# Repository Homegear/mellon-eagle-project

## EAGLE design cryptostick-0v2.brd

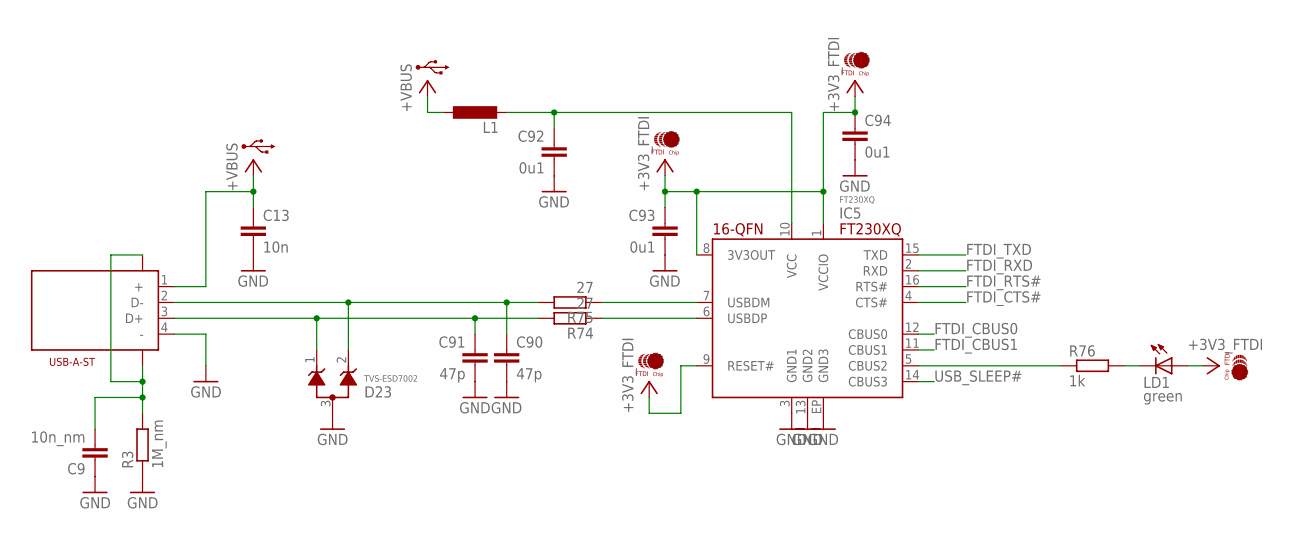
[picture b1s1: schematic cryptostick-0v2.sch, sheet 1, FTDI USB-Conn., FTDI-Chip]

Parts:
C9: 10n_nm; C0603
C13: 10n; R0402-MCU
C90, C91: 47p; R0402-MCU
C92, C93, C94: 0u1; R0402-MCU
D23: TVS-ESD7002; SC70-3
IC5: FT230XQ; 16QFN-FT230X
J1: USB-A-ST
L1: L-EUR0402-MCU; R0402-MCU
LD1: green; 0603-SIDELED-RPI
R3: 1M_nm; R0603
R74, R75: 27; R0402-MCU
R76: 1k; R0402-MCU

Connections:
+3V3_FTDI: C93.1, C94.1, IC5.1 (VCCIO), IC5.8 (3V3OUT), IC5.9 (RESET#), LD1.A; also elsewhere on the board
+5V_FTDI: C92.1, IC5.10 (VCC), L1.2
+VBUS: C13.1, J1.1 (+), L1.1; also elsewhere on the board
FTDI_CBUS0: IC5.12 (CBUS0); also elsewhere on the board
FTDI_CBUS1: IC5.11 (CBUS1); also elsewhere on the board
FTDI_CTS#: IC5.4 (CTS#); also elsewhere on the board
FTDI_RTS#: IC5.16 (RTS#); also elsewhere on the board
FTDI_RXD: IC5.2 (RXD); also elsewhere on the board
FTDI_TXD: IC5.15 (TXD); also elsewhere on the board
FTDI_TXLED#: IC5.5 (CBUS2), R76.1
GND: C9.1, C13.2, C90.2, C91.2, C92.2, C93.2, C94.2, D23.3, IC5.3 (GND1), IC5.13 (GND2), IC5.EP (GND3), J1.4 (-), R3.1; also elsewhere on the board
unnamed: LD1.C, R76.2
unnamed: IC5.7 (USBDM), R75.1
unnamed: IC5.6 (USBDP), R74.1
unnamed: C91.1, D23.1, J1.3 (D+), R74.2
unnamed: C90.1, D23.2, J1.2 (D-), R75.2
USB_SHLD: C9.2, J1.SH1, J1.SH2, R3.2
USB_SLEEP#: IC5.14 (CBUS3); also elsewhere on the board

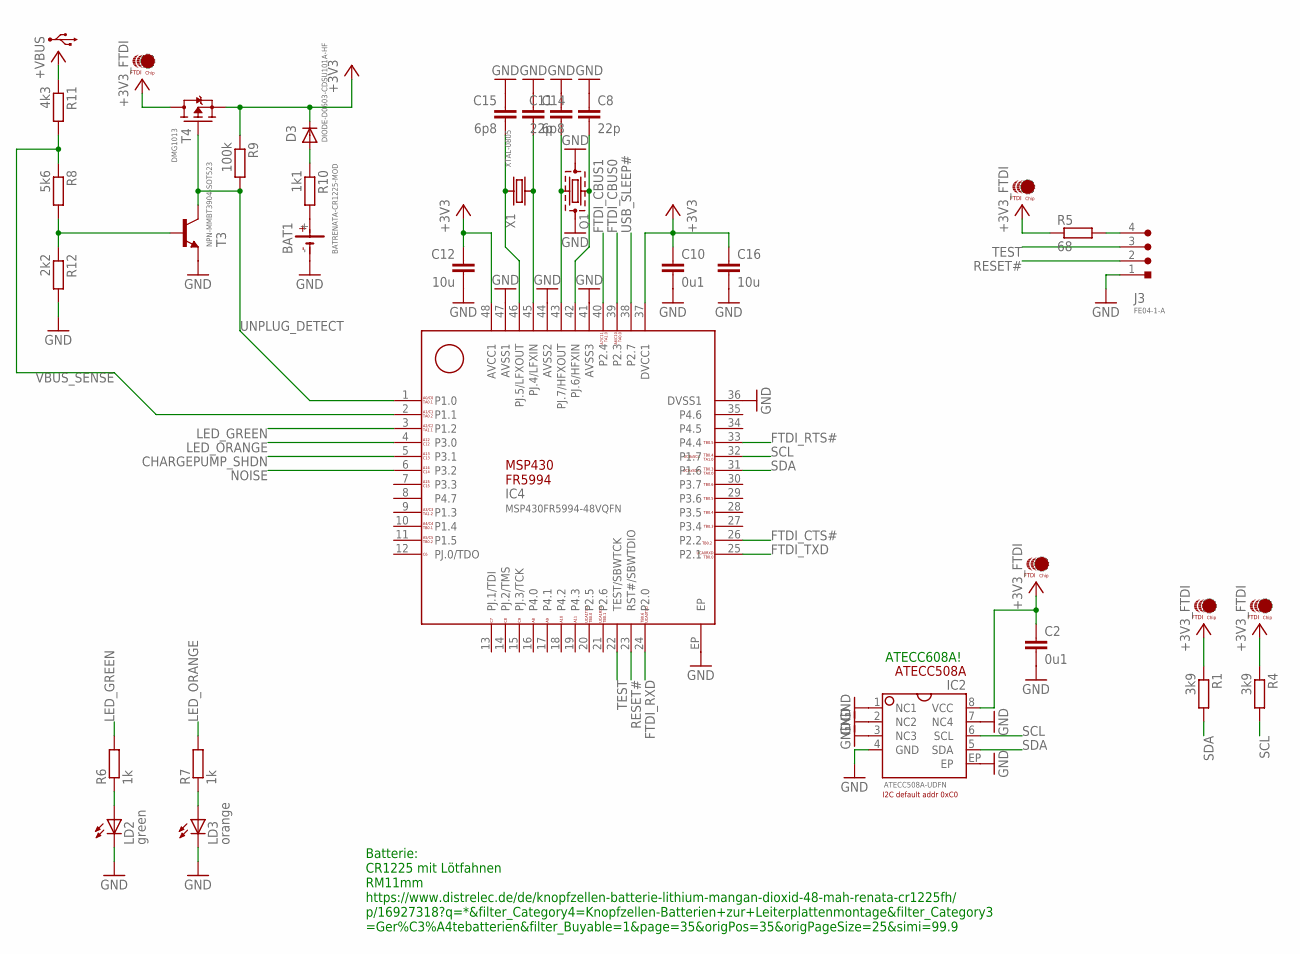
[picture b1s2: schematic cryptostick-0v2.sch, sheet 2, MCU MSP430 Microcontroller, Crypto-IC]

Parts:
BAT1: BATRENATA-CR1225-MOD; BAT-RENATA-CR1225-MOD
C2, C10: 0u1; R0402-MCU
C8, C11: 22p; R0402-MCU
C12, C16: 10u; R0603-MCU
C14, C15: 6p8; R0402-MCU
D3: DIODE-D0603-CDSU101A-HF; D-D0603
IC2: ATECC508A-UDFN; 8UDFN
IC4: MSP430FR5994-48VQFN; 48VQFN-MSP430FR5994
J3: FE04-1-A; FE04-1A
LD2: green; 0603-SIDELED-RPI
LD3: orange; 0603-SIDELED-RPI
Q1: XTAL-2.0X1.6-MOD
R1, R4: 3k9; R0402-MCU
R5: 68; R0402-MCU
R6, R7: 1k; R0402-MCU
R8: 5k6; R0402-MCU
R9: 100k; R0402-MCU
R10: 1k1; R0402-MCU
R11: 4k3; R0402-MCU
R12: 2k2; R0402-MCU
T3: NPN-MMBT3904-SOT523; SOT523
T4: DMG1013; SC70-3
X1: XTAL-0805; XTAL-32KHZ-0805

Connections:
+3V3: C10.1, C12.1, C16.1, D3.C, IC4.37 (DVCC1), IC4.48 (AVCC1), R9.1, T4.2 (S)
+3V3_FTDI: C2.1, IC2.8 (VCC), R1.1, R4.1, R5.1, T4.3 (D); also elsewhere on the board
+VBUS: R11.1; also elsewhere on the board
CHARGEPUMP_SHDN: IC4.5 (P3.1); also elsewhere on the board
FTDI_CBUS0: IC4.39 (P2.3); also elsewhere on the board
FTDI_CBUS1: IC4.40 (P2.4); also elsewhere on the board
FTDI_CTS#: IC4.26 (P2.2); also elsewhere on the board
FTDI_RTS#: IC4.33 (P4.4); also elsewhere on the board
FTDI_RXD: IC4.24 (P2.0); also elsewhere on the board
FTDI_TXD: IC4.25 (P2.1); also elsewhere on the board
GND: BAT1.-, C2.2, C8.1, C10.2, C11.1, C12.2, C14.1, C15.1, C16.2, IC2.1 (NC1), IC2.2 (NC2), IC2.3 (NC3), IC2.4 (GND), IC2.7 (NC4), IC2.EP, IC4.36 (DVSS1), IC4.41 (AVSS3), IC4.44 (AVSS2), IC4.47 (AVSS1), IC4.EP, J3.1, LD2.C, LD3.C, Q1.2 (GND1), Q1.4 (GND2), R12.2, T3.2 (E); also elsewhere on the board
LED_GREEN: IC4.3 (P1.2), R6.2
LED_ORANGE: IC4.4 (P3.0), R7.2
unnamed: J3.4, R5.2
unnamed: LD3.A, R7.1
unnamed: LD2.A, R6.1
unnamed: C11.2, IC4.43 (PJ.7/HFXOUT), Q1.1
unnamed: C8.2, IC4.42 (PJ.6/HFXIN), Q1.3 (2)
unnamed: D3.A, R10.1
unnamed: C14.2, IC4.45 (PJ.4/LFXIN), X1.P$1 (1)
unnamed: BAT1.+, R10.2
unnamed: R8.2, R12.1, T3.1 (B)
unnamed: C15.2, IC4.46 (PJ.5/LFXOUT), X1.P$2 (2)
NOISE: IC4.6 (P3.2); also elsewhere on the board
RESET#: IC4.23 (RST#/SBWTDIO), J3.2
SCL: IC2.6 (SCL), IC4.32 (P1.7), R4.2
SDA: IC2.5 (SDA), IC4.31 (P1.6), R1.2
TEST: IC4.22 (TEST/SBWTCK), J3.3
UNPLUG_DETECT: IC4.1 (P1.0), R9.2, T3.3 (C), T4.1 (G)
USB_SLEEP#: IC4.38 (P2.7); also elsewhere on the board
VBUS_SENSE: IC4.2 (P1.1), R8.1, R11.2

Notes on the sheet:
ATECC608A!
Batterie: CR1225 mit Lötfahnen RM11mm https://www.distrelec.de/de/knopfzellen-batterie-lithium-mangan-dioxid-48-mah-renata-cr1225fh/ p/16927318?q=*&filter_Category4=Knopfzellen-Batterien+zur+Leiterplattenmontage&filter_Category3 =Ger%C3%A4tebatterien&filter_Buyable=1&page=35&origPos=35&origPageSize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

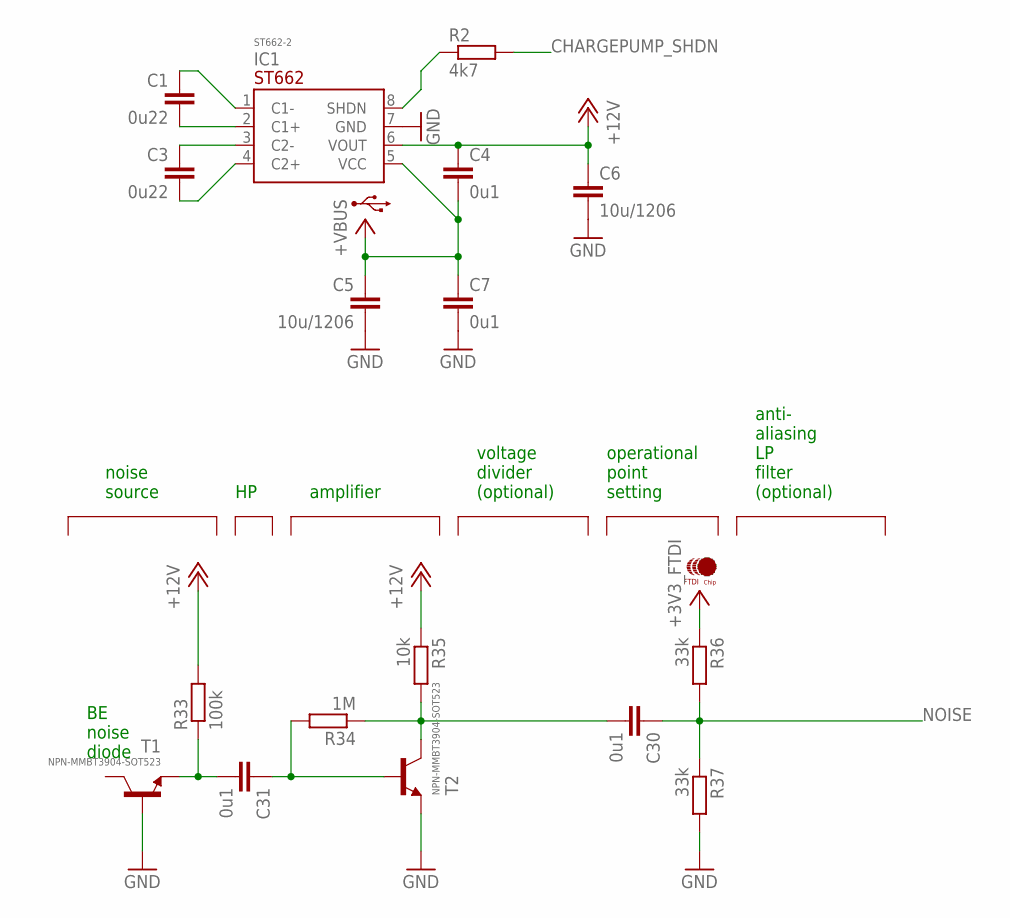
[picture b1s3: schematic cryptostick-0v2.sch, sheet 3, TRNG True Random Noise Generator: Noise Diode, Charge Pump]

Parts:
C1, C3: 0u22; C0603
C4, C7, C30, C31: 0u1; R0402-MCU
C5, C6: 10u/1206; C1206
IC1: ST662-2; 8SOIC-2
R2: 4k7; R0402-MCU
R33: 100k; R0402-MCU
R34: 1M; R0402-MCU
R35: 10k; R0402-MCU
R36, R37: 33k; R0402-MCU
T1, T2: NPN-MMBT3904-SOT523; SOT523

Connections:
+3V3_FTDI: R36.1; also elsewhere on the board
+12V: C4.1, C6.1, IC1.6 (VOUT), R33.2, R35.1
+VBUS: C4.2, C5.1, C7.1, IC1.5 (VCC); also elsewhere on the board
CHARGEPUMP_SHDN: R2.2; also elsewhere on the board
GND: C5.2, C6.2, C7.2, IC1.7 (GND), R37.2, T1.1 (B), T2.2 (E); also elsewhere on the board
unnamed: C31.1, R34.2, T2.1 (B)
unnamed: C30.2, R34.1, R35.2, T2.3 (C)
unnamed: C3.1, IC1.3 (C2-)
unnamed: C1.2, IC1.2 (C1+)
unnamed: C1.1, IC1.1 (C1-)
unnamed: C3.2, IC1.4 (C2+)
unnamed: IC1.8 (SHDN), R2.1
unnamed: C31.2, R33.1, T1.2 (E)
NOISE: C30.1, R36.2, R37.1; also elsewhere on the board

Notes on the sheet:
operational point setting
voltage divider (optional)
anti- aliasing LP filter (optional)
BE noise diode
noise source
amplifier

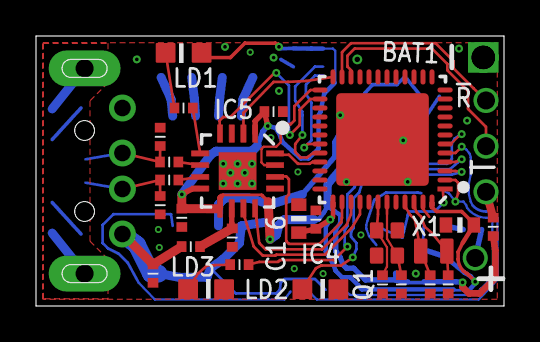
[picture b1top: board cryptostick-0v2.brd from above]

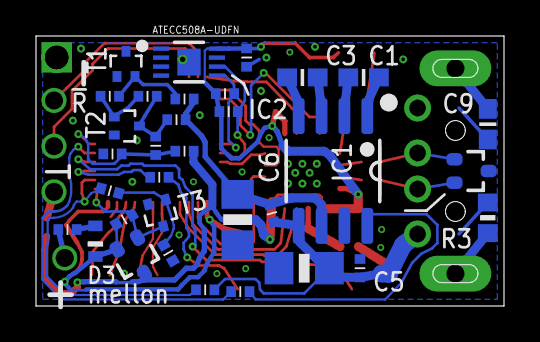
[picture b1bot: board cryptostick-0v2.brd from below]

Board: 2 copper layers, 26.0 x 15.0 mm, 62 parts (33 on the bottom side), 48 nets.

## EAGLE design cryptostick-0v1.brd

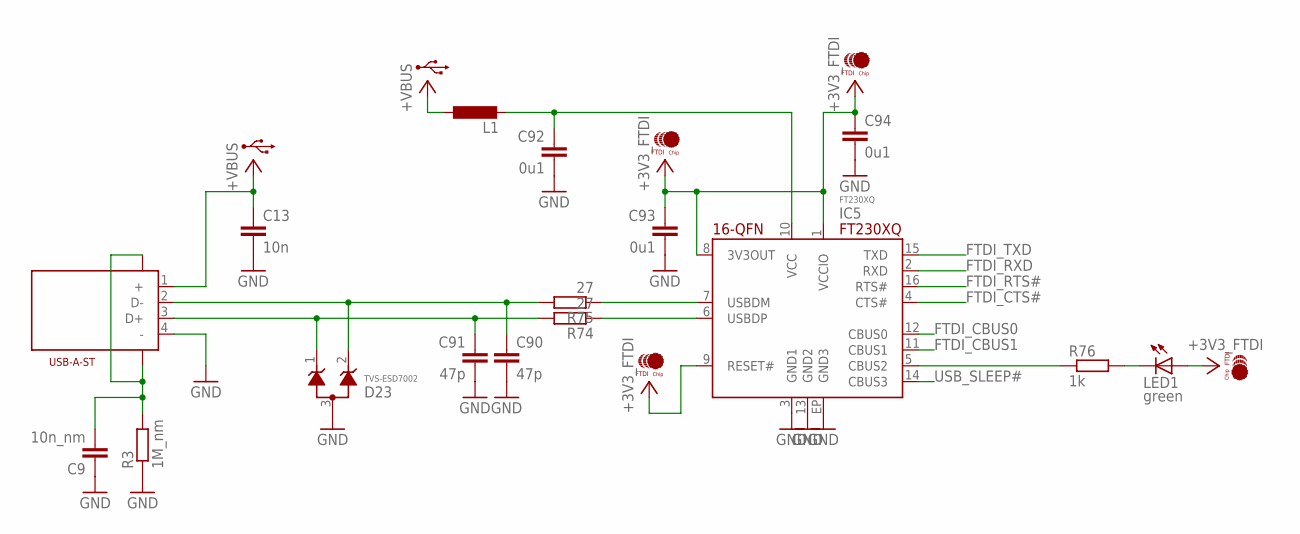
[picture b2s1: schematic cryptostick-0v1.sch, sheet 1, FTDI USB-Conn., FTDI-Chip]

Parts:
C9: 10n_nm; C0603
C13: 10n; R0402-MCU
C90, C91: 47p; R0402-MCU
C92, C93, C94: 0u1; R0402-MCU
D23: TVS-ESD7002; SC70-3
IC5: FT230XQ; 16QFN-FT230X
J1: USB-A-ST
L1: L-EUR0402-MCU; R0402-MCU
LED1: green; 0603-SIDELED-RPI
R3: 1M_nm; R0603
R74, R75: 27; R0402-MCU
R76: 1k; R0402-MCU

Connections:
+3V3_FTDI: C93.1, C94.1, IC5.1 (VCCIO), IC5.8 (3V3OUT), IC5.9 (RESET#), LED1.A; also elsewhere on the board
+5V_FTDI: C92.1, IC5.10 (VCC), L1.2
+VBUS: C13.1, J1.1 (+), L1.1; also elsewhere on the board
FTDI_CBUS0: IC5.12 (CBUS0); also elsewhere on the board
FTDI_CBUS1: IC5.11 (CBUS1); also elsewhere on the board
FTDI_CTS#: IC5.4 (CTS#); also elsewhere on the board
FTDI_RTS#: IC5.16 (RTS#); also elsewhere on the board
FTDI_RXD: IC5.2 (RXD); also elsewhere on the board
FTDI_TXD: IC5.15 (TXD); also elsewhere on the board
FTDI_TXLED#: IC5.5 (CBUS2), R76.1
GND: C9.1, C13.2, C90.2, C91.2, C92.2, C93.2, C94.2, D23.3, IC5.3 (GND1), IC5.13 (GND2), IC5.EP (GND3), J1.4 (-), R3.1; also elsewhere on the board
unnamed: LED1.C, R76.2
unnamed: IC5.7 (USBDM), R75.1
unnamed: IC5.6 (USBDP), R74.1
unnamed: C91.1, D23.1, J1.3 (D+), R74.2
unnamed: C90.1, D23.2, J1.2 (D-), R75.2
USB_SHLD: C9.2, J1.SH1, J1.SH2, R3.2
USB_SLEEP#: IC5.14 (CBUS3); also elsewhere on the board

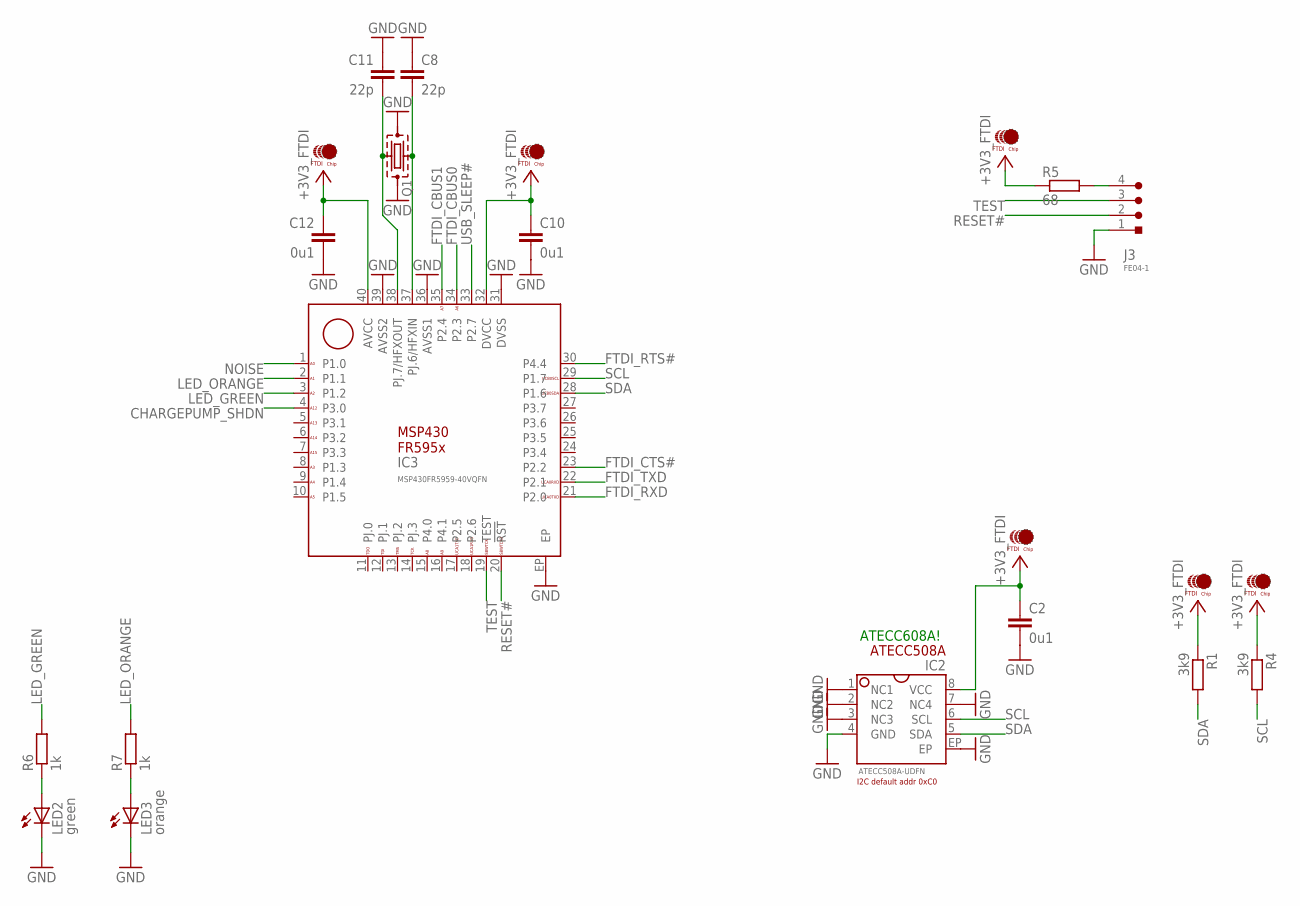
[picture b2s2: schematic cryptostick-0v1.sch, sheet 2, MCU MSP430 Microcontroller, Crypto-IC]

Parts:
C2, C10, C12: 0u1; R0402-MCU
C8, C11: 22p; R0402-MCU
IC2: ATECC508A-UDFN; 8UDFN
IC3: MSP430FR5959-40VQFN; 40VQFN-MSP430FR5959
J3: FE04-1
LED2: green; 0603-SIDELED-RPI
LED3: orange; 0603-SIDELED-RPI
Q1: XTAL-2.0X1.6; XTAL-30MHZ-2.0X1.6
R1, R4: 3k9; R0402-MCU
R5: 68; R0402-MCU
R6, R7: 1k; R0402-MCU

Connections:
+3V3_FTDI: C2.1, C10.1, C12.1, IC2.8 (VCC), IC3.32 (DVCC), IC3.40 (AVCC), R1.1, R4.1, R5.1; also elsewhere on the board
CHARGEPUMP_SHDN: IC3.4 (P3.0); also elsewhere on the board
FTDI_CBUS0: IC3.34 (P2.3); also elsewhere on the board
FTDI_CBUS1: IC3.35 (P2.4); also elsewhere on the board
FTDI_CTS#: IC3.23 (P2.2); also elsewhere on the board
FTDI_RTS#: IC3.30 (P4.4); also elsewhere on the board
FTDI_RXD: IC3.21 (P2.0); also elsewhere on the board
FTDI_TXD: IC3.22 (P2.1); also elsewhere on the board
GND: C2.2, C8.1, C10.2, C11.1, C12.2, IC2.1 (NC1), IC2.2 (NC2), IC2.3 (NC3), IC2.4 (GND), IC2.7 (NC4), IC2.EP, IC3.31 (DVSS), IC3.36 (AVSS1), IC3.39 (AVSS2), IC3.EP, J3.1, LED2.C, LED3.C, Q1.2 (GND1), Q1.4 (GND2); also elsewhere on the board
LED_GREEN: IC3.3 (P1.2), R6.2
LED_ORANGE: IC3.2 (P1.1), R7.2
unnamed: J3.4, R5.2
unnamed: LED3.A, R7.1
unnamed: LED2.A, R6.1
unnamed: C11.2, IC3.38 (PJ.7/HFXOUT), Q1.1
unnamed: C8.2, IC3.37 (PJ.6/HFXIN), Q1.3 (2)
NOISE: IC3.1 (P1.0); also elsewhere on the board
RESET#: IC3.20 (!RST), J3.2
SCL: IC2.6 (SCL), IC3.29 (P1.7), R4.2
SDA: IC2.5 (SDA), IC3.28 (P1.6), R1.2
TEST: IC3.19 (TEST), J3.3
USB_SLEEP#: IC3.33 (P2.7); also elsewhere on the board

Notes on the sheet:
ATECC608A!

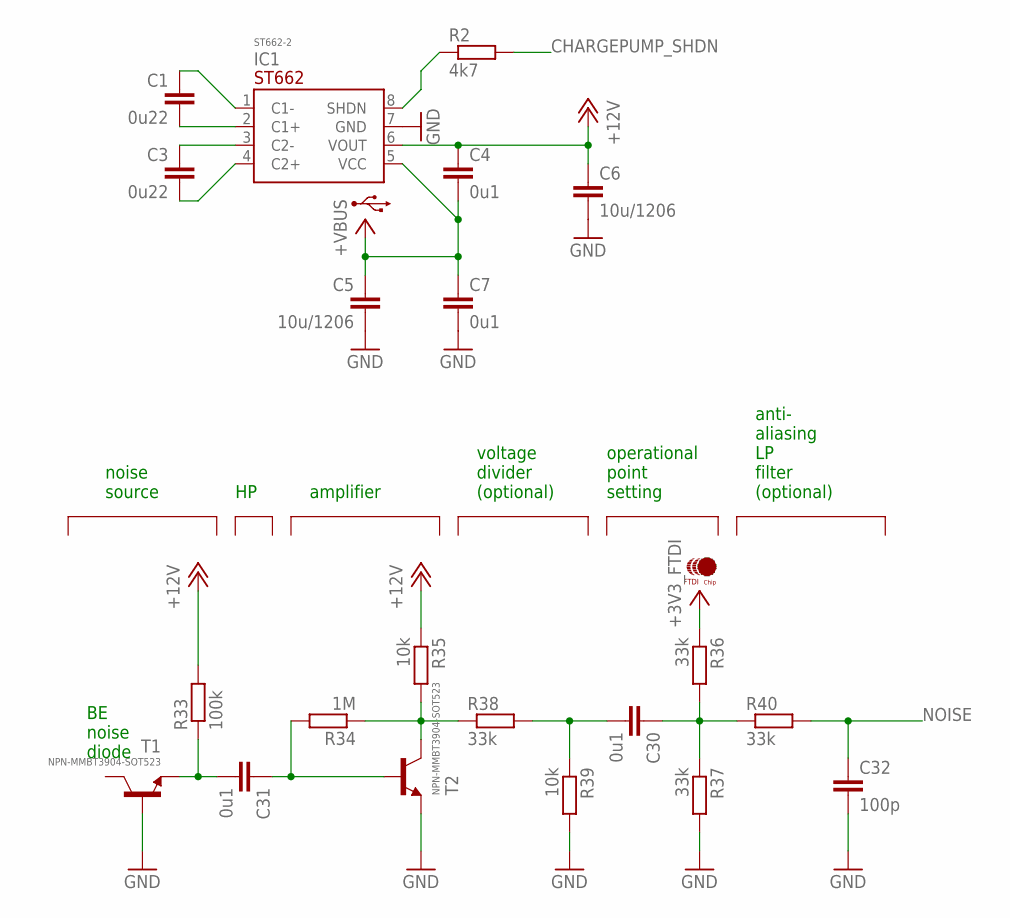
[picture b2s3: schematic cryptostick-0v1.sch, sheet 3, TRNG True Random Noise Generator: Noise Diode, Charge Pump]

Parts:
C1, C3: 0u22; C0603
C4, C7, C30, C31: 0u1; R0402-MCU
C5, C6: 10u/1206; C1206
C32: 100p; R0402-MCU
IC1: ST662-2; 8SOIC-2
R2: 4k7; R0402-MCU
R33: 100k; R0402-MCU
R34: 1M; R0402-MCU
R35, R39: 10k; R0402-MCU
R36, R37, R38, R40: 33k; R0402-MCU
T1, T2: NPN-MMBT3904-SOT523; SOT523

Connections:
+3V3_FTDI: R36.1; also elsewhere on the board
+12V: C4.1, C6.1, IC1.6 (VOUT), R33.2, R35.1
+VBUS: C4.2, C5.1, C7.1, IC1.5 (VCC); also elsewhere on the board
CHARGEPUMP_SHDN: R2.2; also elsewhere on the board
GND: C5.2, C6.2, C7.2, C32.2, IC1.7 (GND), R37.2, R39.2, T1.1 (B), T2.2 (E); also elsewhere on the board
unnamed: C31.1, R34.2, T2.1 (B)
unnamed: R34.1, R35.2, R38.1, T2.3 (C)
unnamed: C3.1, IC1.3 (C2-)
unnamed: C1.2, IC1.2 (C1+)
unnamed: C1.1, IC1.1 (C1-)
unnamed: C3.2, IC1.4 (C2+)
unnamed: IC1.8 (SHDN), R2.1
unnamed: C31.2, R33.1, T1.2 (E)
unnamed: C30.1, R36.2, R37.1, R40.1
unnamed: C30.2, R38.2, R39.1
NOISE: C32.1, R40.2; also elsewhere on the board

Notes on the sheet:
operational point setting
voltage divider (optional)
anti- aliasing LP filter (optional)
BE noise diode
noise source
amplifier

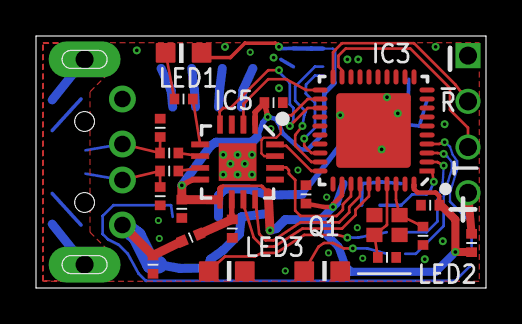
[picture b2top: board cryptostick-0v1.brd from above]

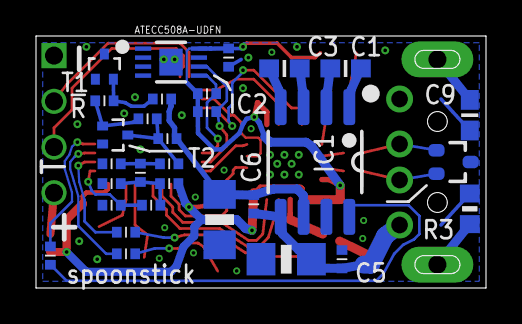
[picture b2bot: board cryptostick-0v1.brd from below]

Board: 2 copper layers, 25.0 x 14.0 mm, 53 parts (30 on the bottom side), 42 nets.
